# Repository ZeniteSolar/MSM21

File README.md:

# MSM21
Modulo de separação dos modulos

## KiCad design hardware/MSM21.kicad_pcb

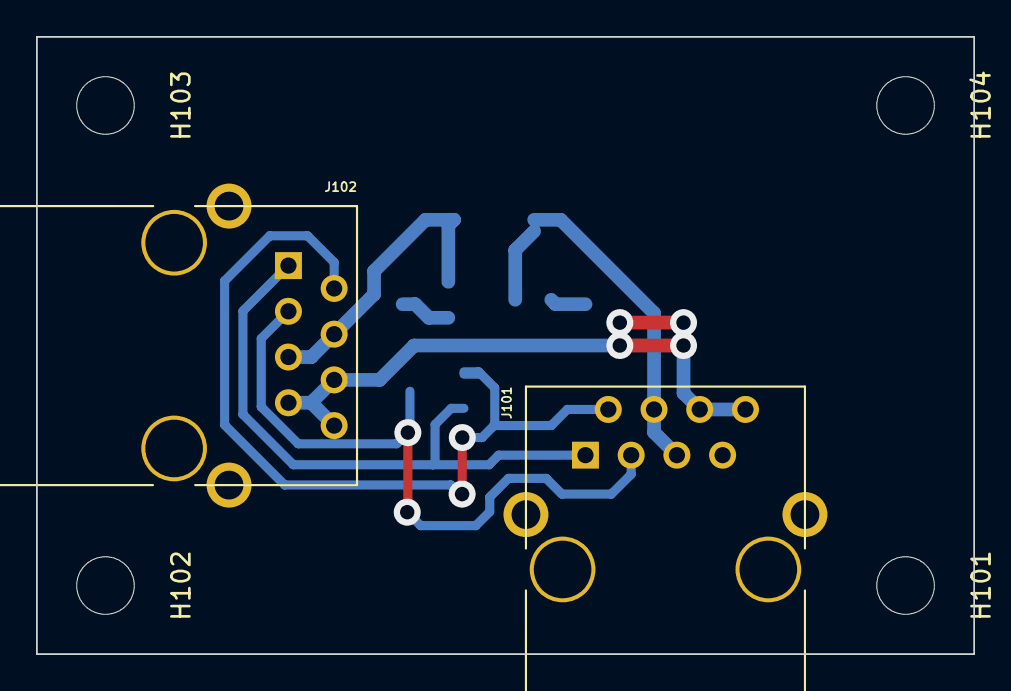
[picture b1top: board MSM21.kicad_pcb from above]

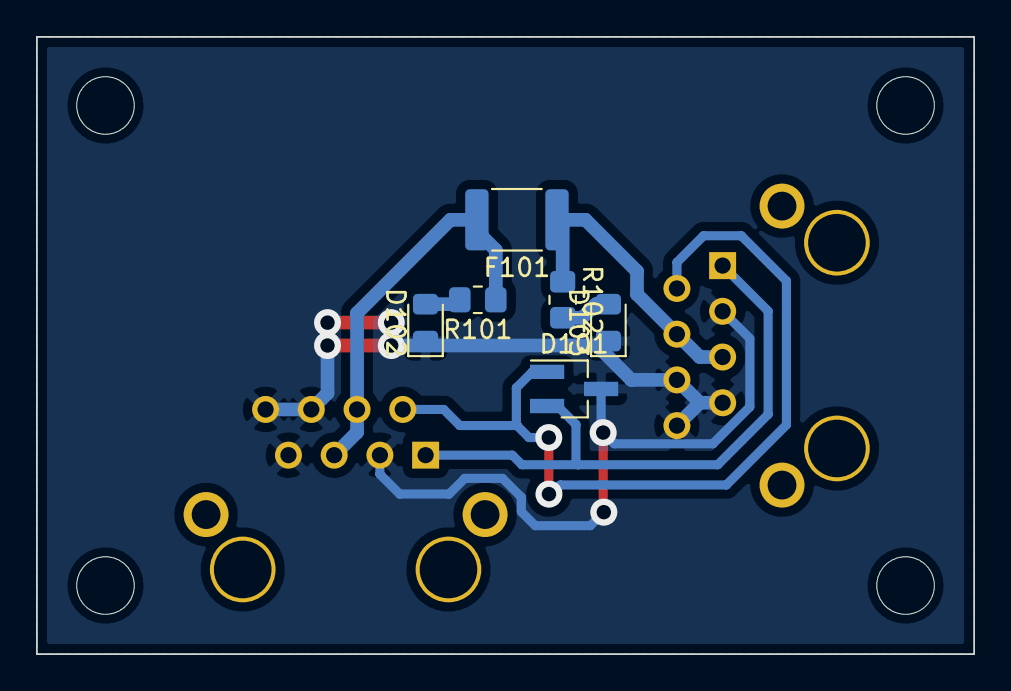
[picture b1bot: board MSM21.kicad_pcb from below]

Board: 2 copper layers, 52.1 x 34.3 mm, 12 parts (6 on the bottom side), 7 nets.

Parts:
D101: pesd1can; SOT-23_Handsoldering
D102: Verde; LED_0805_2012Metric_Pad1.15x1.40mm_HandSolder
D103: Vermelho; LED_0805_2012Metric_Pad1.15x1.40mm_HandSolder
F101: Fuse 1A; Fuse_1812_4532Metric_Pad1.30x3.40mm_HandSolder
H101, H102, H103, H104: MountingHole; MountingHole_3.2mm_M3
J101, J102: RJ45; RJ45_YH59_01
R101, R102: 3k3; R_0805_2012Metric_Pad1.20x1.40mm_HandSolder

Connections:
/CAN_18V: F101.2, J101.4, J101.5, R101.1
/CAN_18V_U: F101.1, J102.4, J102.5, R102.1
/CAN_H: D101.2, J101.1, J102.1
/CAN_L: D101.1, J101.2, J102.2
GND: D101.3, D102.1, D103.1, J101.3, J101.6, J101.7, J101.8, J102.3, J102.6, J102.7, J102.8
unnamed: D102.2, R101.2
unnamed: D103.2, R102.2

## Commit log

2021-09-09 Foi criado o esquematico e a PCB
2021-09-09 Foi gerado o PDF
